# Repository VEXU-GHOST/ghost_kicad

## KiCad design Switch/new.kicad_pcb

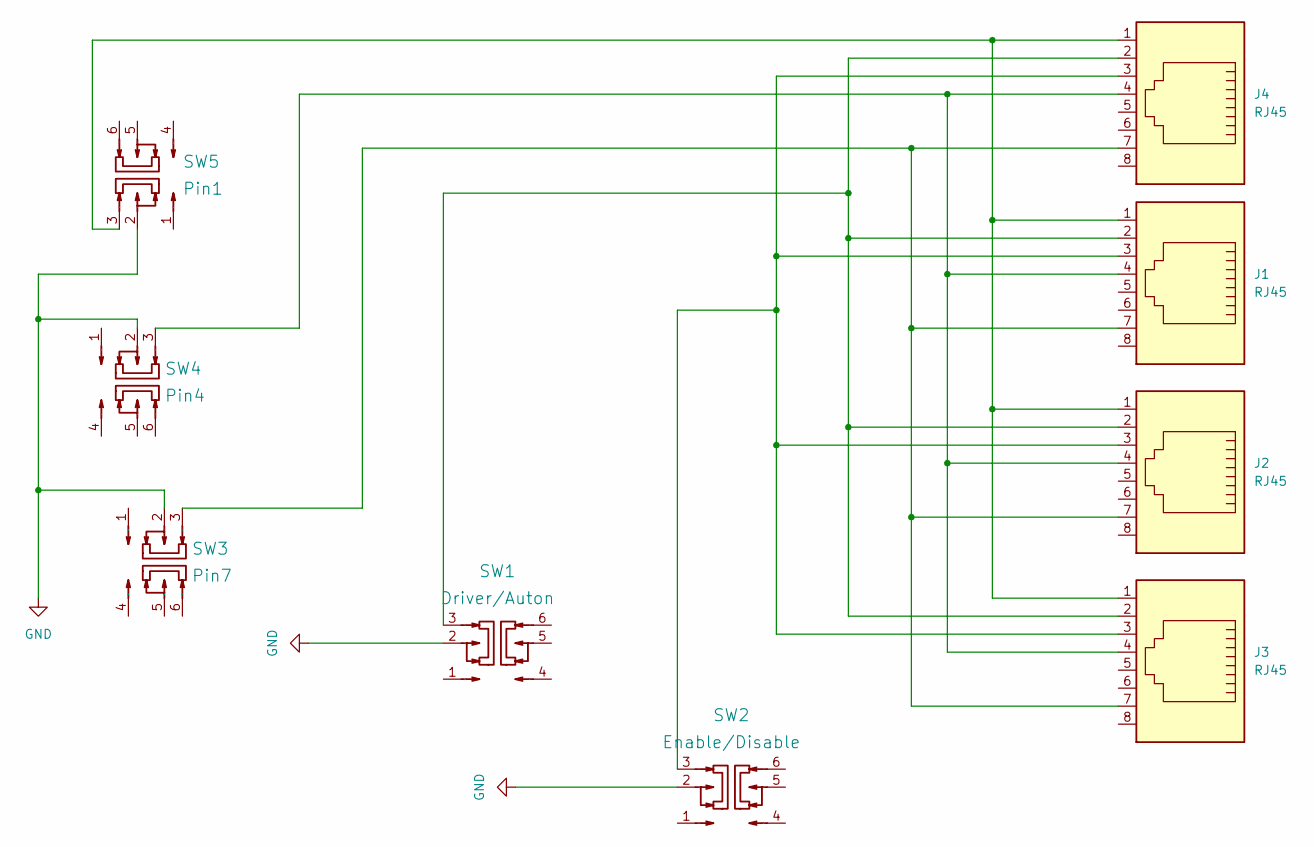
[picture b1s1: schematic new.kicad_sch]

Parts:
J1, J2, J3, J4: RJ45; RJ45-TH_RC0139
SW1: Driver/Auton; SW-SMD_MS-22D28-G020; Manufacturer Part MS-22D28-G020
SW2: Enable/Disable; SW-SMD_MS-22D28-G020; Manufacturer Part MS-22D28-G020
SW3: Pin7; SW-SMD_MS-22D28-G020; Manufacturer Part MS-22D28-G020
SW4: Pin4; SW-SMD_MS-22D28-G020; Manufacturer Part MS-22D28-G020
SW5: Pin1; SW-SMD_MS-22D28-G020; Manufacturer Part MS-22D28-G020

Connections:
GND: SW1.2, SW2.2, SW3.2, SW4.2, SW5.2
unnamed: J1.1, J2.1, J3.1, J4.1, SW5.3
unnamed: J1.2, J2.2, J3.2, J4.2, SW1.3
unnamed: J1.3, J2.3, J3.3, J4.3, SW2.3
unnamed: J1.4, J2.4, J3.4, J4.4, SW4.3
unnamed: J1.7, J2.7, J3.7, J4.7, SW3.3

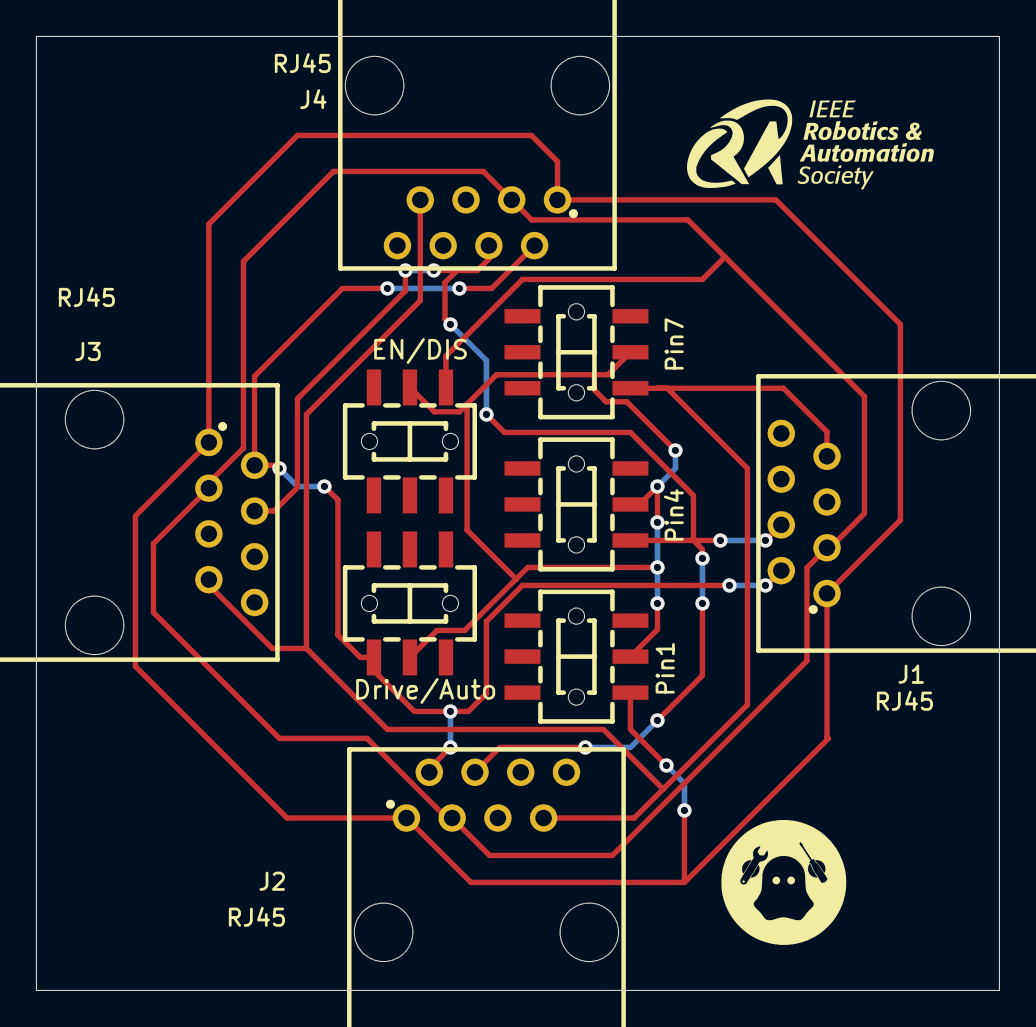
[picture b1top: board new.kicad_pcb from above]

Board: 2 copper layers, 53.5 x 53.0 mm, 9 parts (0 on the bottom side), 6 nets.

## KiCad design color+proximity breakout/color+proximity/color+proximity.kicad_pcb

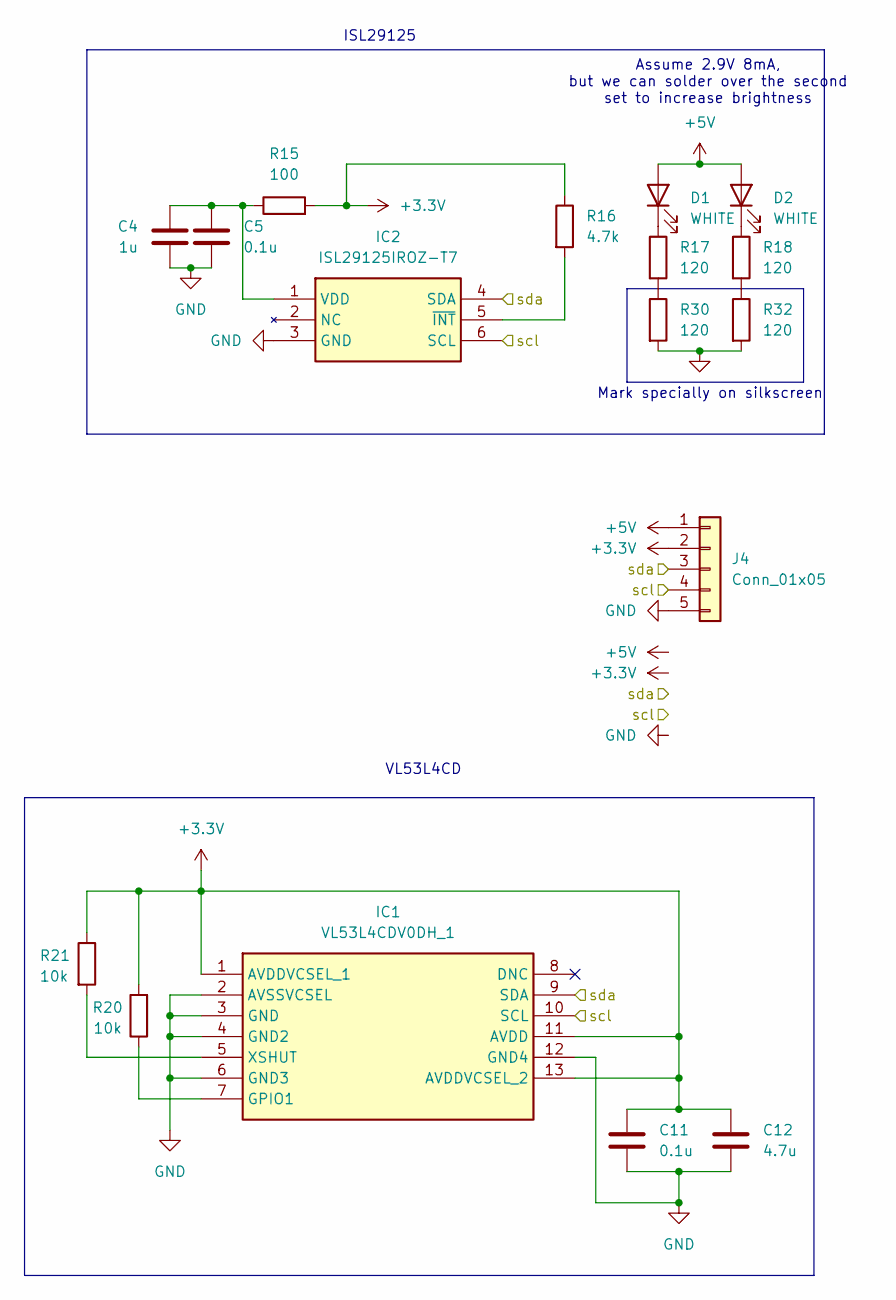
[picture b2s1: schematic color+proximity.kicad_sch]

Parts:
C4: 1u; C_0603_1608Metric_Pad1.08x0.95mm_HandSolder; JLCPCB Part C15849
C5, C11: 0.1u; C_0402_1005Metric_Pad0.74x0.62mm_HandSolder; JLCPCB Part C307331
C12: 4.7u; C_0603_1608Metric_Pad1.08x0.95mm_HandSolder; JLCPCB Part C19666
D1, D2: WHITE; LED_0805_2012Metric_Pad1.15x1.40mm_HandSolder; JLCPCB Part C34499
IC1: VL53L4CDV0DH_1; VL53L4CDV0DH1; Manufacturer_Part_Number VL53L4CDV0DH/1; Mouser Part Number 511-VL53L4CDV0DH/1
IC2: ISL29125IROZ-T7; ISL29125IROZT7; Manufacturer_Part_Number ISL29125IROZ-T7; Mouser Part Number 968-ISL29125IROZ-T7
J4: Conn_01x05; PinHeader_1x05_P2.54mm_Vertical
R15: 100; R_0402_1005Metric_Pad0.72x0.64mm_HandSolder; Manufacturer_Part_Number 0402WGF1000TCE; JLCPCB Part 0402WGF1000TCE
R16: 4.7k; R_0402_1005Metric_Pad0.72x0.64mm_HandSolder; Manufacturer_Part_Number 0402WGF4701TCE; JLCPCB Part 0402WGF4701TCE
R17, R18, R30, R32: 120; R_0402_1005Metric; Manufacturer_Part_Number 0402WGF1200TCE; JLCPCB Part 0402WGF1200TCE
R20, R21: 10k; R_0402_1005Metric_Pad0.72x0.64mm_HandSolder; Manufacturer_Part_Number 0402WGF1002TCE; JLCPCB Part 0402WGF1002TCE

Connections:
+3.3V: C11.1, C12.1, IC1.1 (AVDDVCSEL_1), IC1.11 (AVDD), IC1.13 (AVDDVCSEL_2), J4.2, R15.2, R16.1, R20.2, R21.1; also elsewhere on the board
+5V: D1.2 (A), D2.2 (A), J4.1; also elsewhere on the board
/scl: IC1.10 (SCL), IC2.6 (SCL), J4.4; also elsewhere on the board
/sda: IC1.9 (SDA), IC2.4 (SDA), J4.3; also elsewhere on the board
GND: C4.2, C5.2, C11.2, C12.2, IC1.2 (AVSSVCSEL), IC1.3 (GND), IC1.4 (GND2), IC1.6 (GND3), IC1.12 (GND4), IC2.3 (GND), J4.5, R30.2, R32.2; also elsewhere on the board
unnamed: D1.1 (K), R17.1
unnamed: D2.1 (K), R18.1
unnamed: IC1.7 (GPIO1), R20.1
unnamed: IC1.5 (XSHUT), R21.2
unnamed: C4.1, C5.1, IC2.1 (VDD), R15.1
unnamed: IC2.5 (~INT), R16.2
unnamed: R17.2, R30.1
unnamed: R18.2, R32.1

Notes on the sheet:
Mark specially on silkscreen
ISL29125
Assume 2.9V 8mA, but we can solder over the second set to increase brightness
VL53L4CD

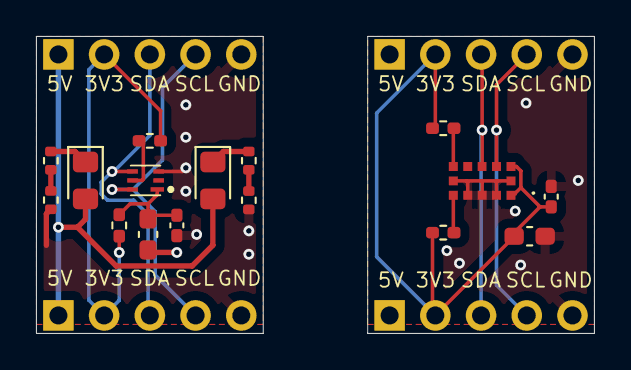
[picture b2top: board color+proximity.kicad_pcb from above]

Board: 2 copper layers, 31.0 x 16.5 mm, 20 parts (0 on the bottom side), 13 nets.

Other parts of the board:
J4#2, J4#3, J4#4: Conn_01x05; PinHeader_1x05_P2.54mm_Vertical

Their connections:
+3.3V: J4#2.2, J4#3.2, J4#4.2; also elsewhere on the board
+5V: J4#2.1, J4#3.1, J4#4.1; also elsewhere on the board
/scl: J4#2.4, J4#3.4, J4#4.4; also elsewhere on the board
/sda: J4#2.3, J4#3.3, J4#4.3; also elsewhere on the board
GND: J4#2.5, J4#3.5, J4#4.5; also elsewhere on the board

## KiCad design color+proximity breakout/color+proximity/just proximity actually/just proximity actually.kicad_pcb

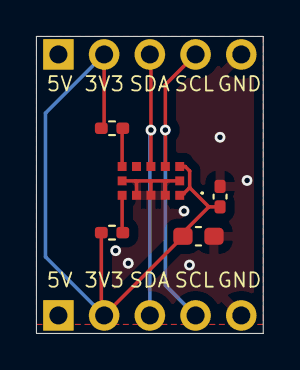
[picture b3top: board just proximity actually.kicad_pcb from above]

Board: 2 copper layers, 12.6 x 16.5 mm, 7 parts (0 on the bottom side), 7 nets.

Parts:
C11: 0.1u; C_0402_1005Metric_Pad0.74x0.62mm_HandSolder
C12: 4.7u; C_0603_1608Metric_Pad1.08x0.95mm_HandSolder
IC1: VL53L4CDV0DH_1; VL53L4CDV0DH1
J4, J4#2: Conn_01x05; PinHeader_1x05_P2.54mm_Vertical
R20, R21: 10k; R_0402_1005Metric_Pad0.72x0.64mm_HandSolder

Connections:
+3.3V: C11.1, C12.1, IC1.1 (AVDDVCSEL_1), IC1.11 (AVDD), IC1.13 (AVDDVCSEL_2), J4.2, J4#2.2, R20.2, R21.1
+5V: J4.1, J4#2.1
/scl: IC1.10 (SCL), J4.4, J4#2.4
/sda: IC1.9 (SDA), J4.3, J4#2.3
GND: C11.2, C12.2, IC1.2 (AVSSVCSEL), IC1.3 (GND), IC1.4 (GND2), IC1.6 (GND3), IC1.12 (GND4), J4.5, J4#2.5
unnamed: IC1.7 (GPIO1), R20.1
unnamed: IC1.5 (XSHUT), R21.2

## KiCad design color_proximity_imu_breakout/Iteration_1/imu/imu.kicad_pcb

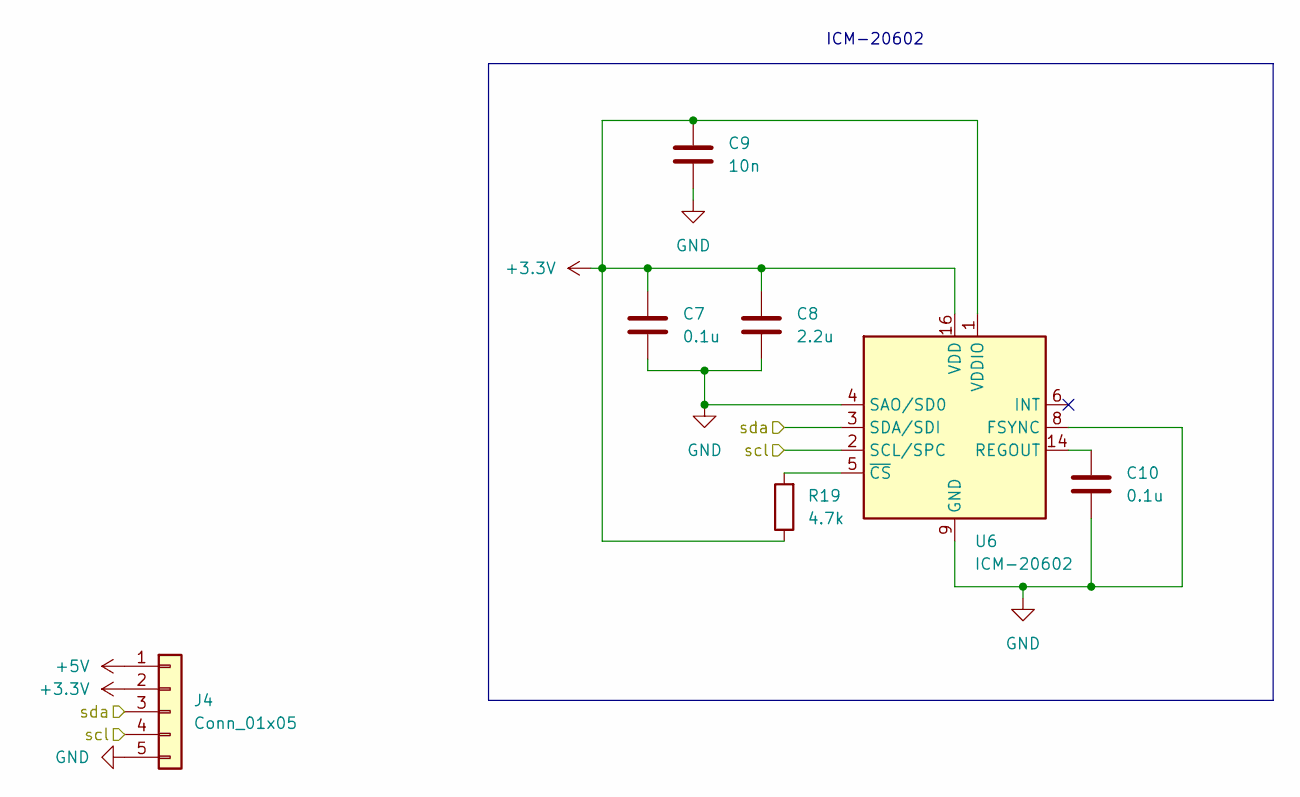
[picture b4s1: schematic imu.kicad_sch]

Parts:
C7, C10: 0.1u; C_0402_1005Metric_Pad0.74x0.62mm_HandSolder; JLCPCB Part C307331
C8: 2.2u; C_0603_1608Metric_Pad1.08x0.95mm_HandSolder; JLCPCB Part C23630
C9: 10n; C_0402_1005Metric_Pad0.74x0.62mm_HandSolder; JLCPCB Part C15195
J4: Conn_01x05; PinHeader_1x05_P2.54mm_Vertical
R19: 4.7k; R_0402_1005Metric_Pad0.72x0.64mm_HandSolder; Manufacturer_Part_Number 0402WGF4701TCE; JLCPCB Part 0402WGF4701TCE
U6: ICM-20602; LGA-16_3x3mm_P0.5mm_LayoutBorder3x5y; Manufacturer_Part_Number ICM-20602; JLCPCB Part C97633

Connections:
+3.3V: C7.1, C8.1, C9.1, J4.2, R19.1, U6.1 (VDDIO), U6.16 (VDD); also elsewhere on the board
+5V: J4.1; also elsewhere on the board
/scl: J4.4, U6.2 (SCL/SPC); also elsewhere on the board
/sda: J4.3, U6.3 (SDA/SDI); also elsewhere on the board
GND: C7.2, C8.2, C9.2, C10.2, J4.5, U6.4 (SAO/SD0), U6.8 (FSYNC), U6.9 (GND), U6.10 (GND), U6.11 (GND), U6.12 (GND), U6.13 (GND), U6.15 (GND); also elsewhere on the board
unnamed: C10.1, U6.14 (REGOUT)
unnamed: R19.2, U6.5 (~CS)

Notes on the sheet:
ICM-20602

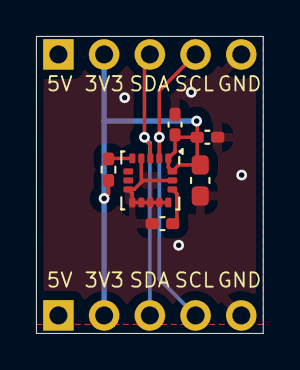
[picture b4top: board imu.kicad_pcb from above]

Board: 2 copper layers, 12.6 x 16.5 mm, 8 parts (0 on the bottom side), 7 nets.

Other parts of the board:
J4#2: Conn_01x05; PinHeader_1x05_P2.54mm_Vertical

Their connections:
+3.3V: J4#2.2; also elsewhere on the board
+5V: J4#2.1; also elsewhere on the board
/scl: J4#2.4; also elsewhere on the board
/sda: J4#2.3; also elsewhere on the board
GND: J4#2.5; also elsewhere on the board
